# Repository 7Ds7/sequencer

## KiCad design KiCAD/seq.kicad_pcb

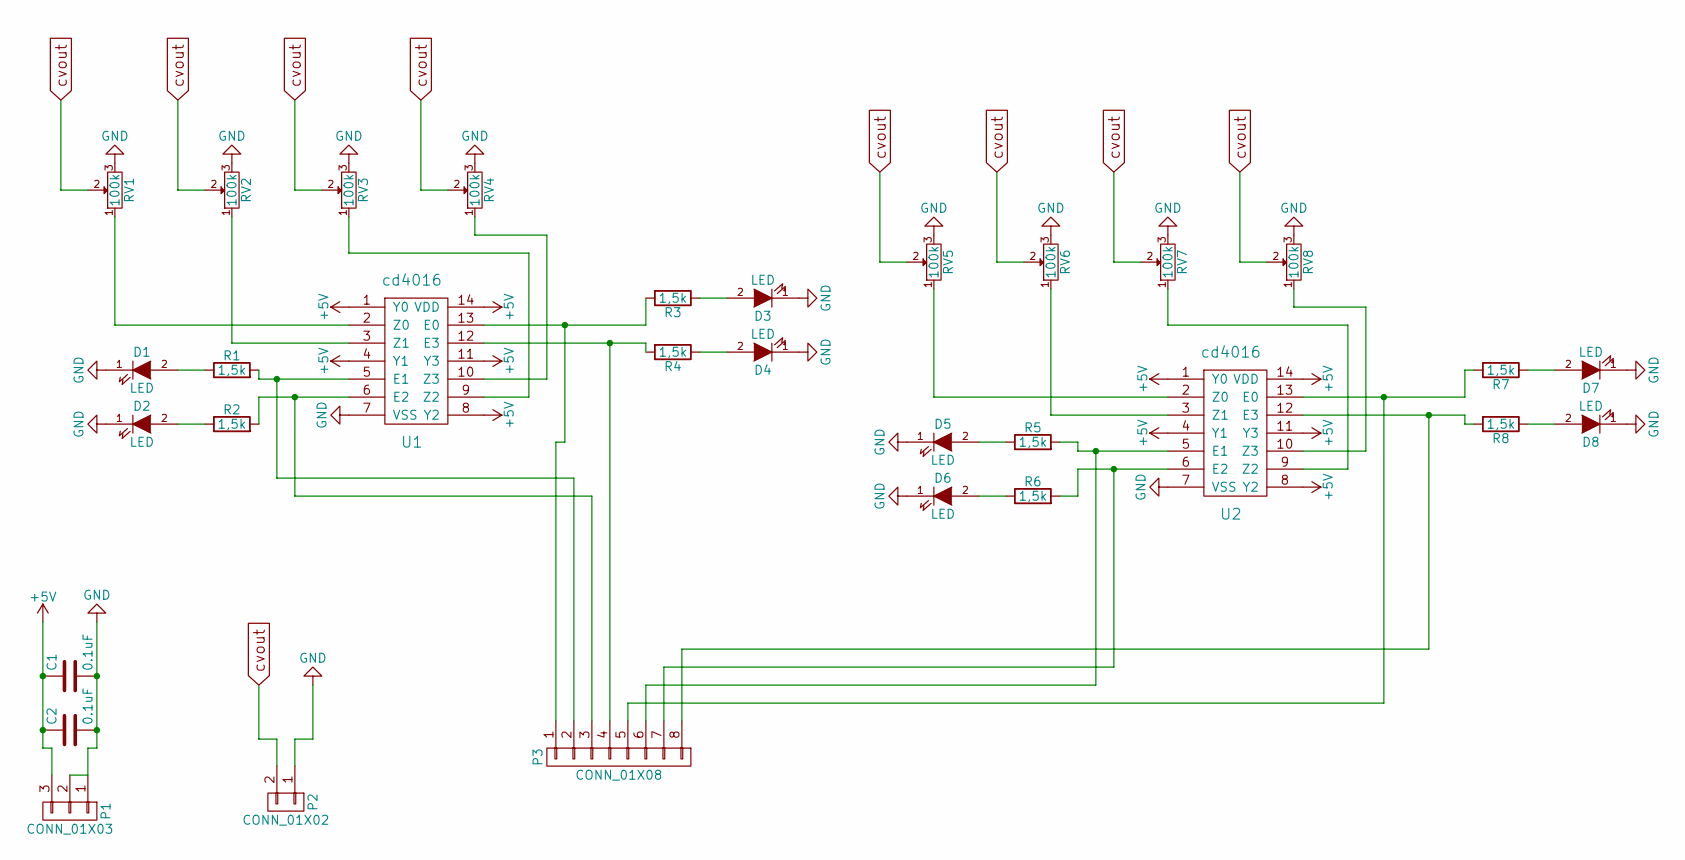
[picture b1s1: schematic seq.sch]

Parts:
C1, C2: 0.1uF; C_Disc_D6_P5
D1, D2, D3, D4, D5, D6, D7, D8: LED; LED-5MM
P1: CONN_01X03; Pin_Header_Straight_1x03
P2: CONN_01X02; Pin_Header_Straight_1x02
P3: CONN_01X08; Pin_Header_Straight_1x08
R1, R2, R3, R4, R5, R6, R7, R8: 1,5k; Resistor_Horizontal_RM15mm
RV1, RV2, RV3, RV4, RV5, RV6, RV7, RV8: 100k; Potentiometer_WirePads_largePads
U1, U2: cd4016; DIP-14_W7.62mm_LongPads

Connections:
+5V: C1.1, C2.1, P1.3, U1.1 (Y0), U1.4 (Y1), U1.8 (Y2), U1.11 (Y3), U1.14 (VDD), U2.1 (Y0), U2.4 (Y1), U2.8 (Y2), U2.11 (Y3), U2.14 (VDD)
GND: C1.2, C2.2, D1.1 (K), D2.1 (K), D3.1 (K), D4.1 (K), D5.1 (K), D6.1 (K), D7.1 (K), D8.1 (K), P1.1, P1.2, P2.1, RV1.3, RV2.3, RV3.3, RV4.3, RV5.3, RV6.3, RV7.3, RV8.3, U1.7 (VSS), U2.7 (VSS)
unnamed: D1.2 (A), R1.1
unnamed: D2.2 (A), R2.1
unnamed: D3.2 (A), R3.1
unnamed: D4.2 (A), R4.1
unnamed: D5.2 (A), R5.1
unnamed: D6.2 (A), R6.1
unnamed: D7.2 (A), R7.1
unnamed: D8.2 (A), R8.1
unnamed: P3.1, R3.2, U1.13 (E0)
unnamed: P3.2, R1.2, U1.5 (E1)
unnamed: P3.3, R2.2, U1.6 (E2)
unnamed: P3.4, R4.2, U1.12 (E3)
unnamed: P3.5, R7.2, U2.13 (E0)
unnamed: P3.6, R5.2, U2.5 (E1)
unnamed: P3.7, R6.2, U2.6 (E2)
unnamed: P3.8, R8.2, U2.12 (E3)
unnamed: RV1.1, U1.2 (Z0)
unnamed: RV2.1, U1.3 (Z1)
unnamed: RV3.1, U1.9 (Z2)
unnamed: RV4.1, U1.10 (Z3)
unnamed: RV5.1, U2.2 (Z0)
unnamed: RV6.1, U2.3 (Z1)
unnamed: RV7.1, U2.9 (Z2)
unnamed: RV8.1, U2.10 (Z3)
cvout: P2.2, RV1.2, RV2.2, RV3.2, RV4.2, RV5.2, RV6.2, RV7.2, RV8.2

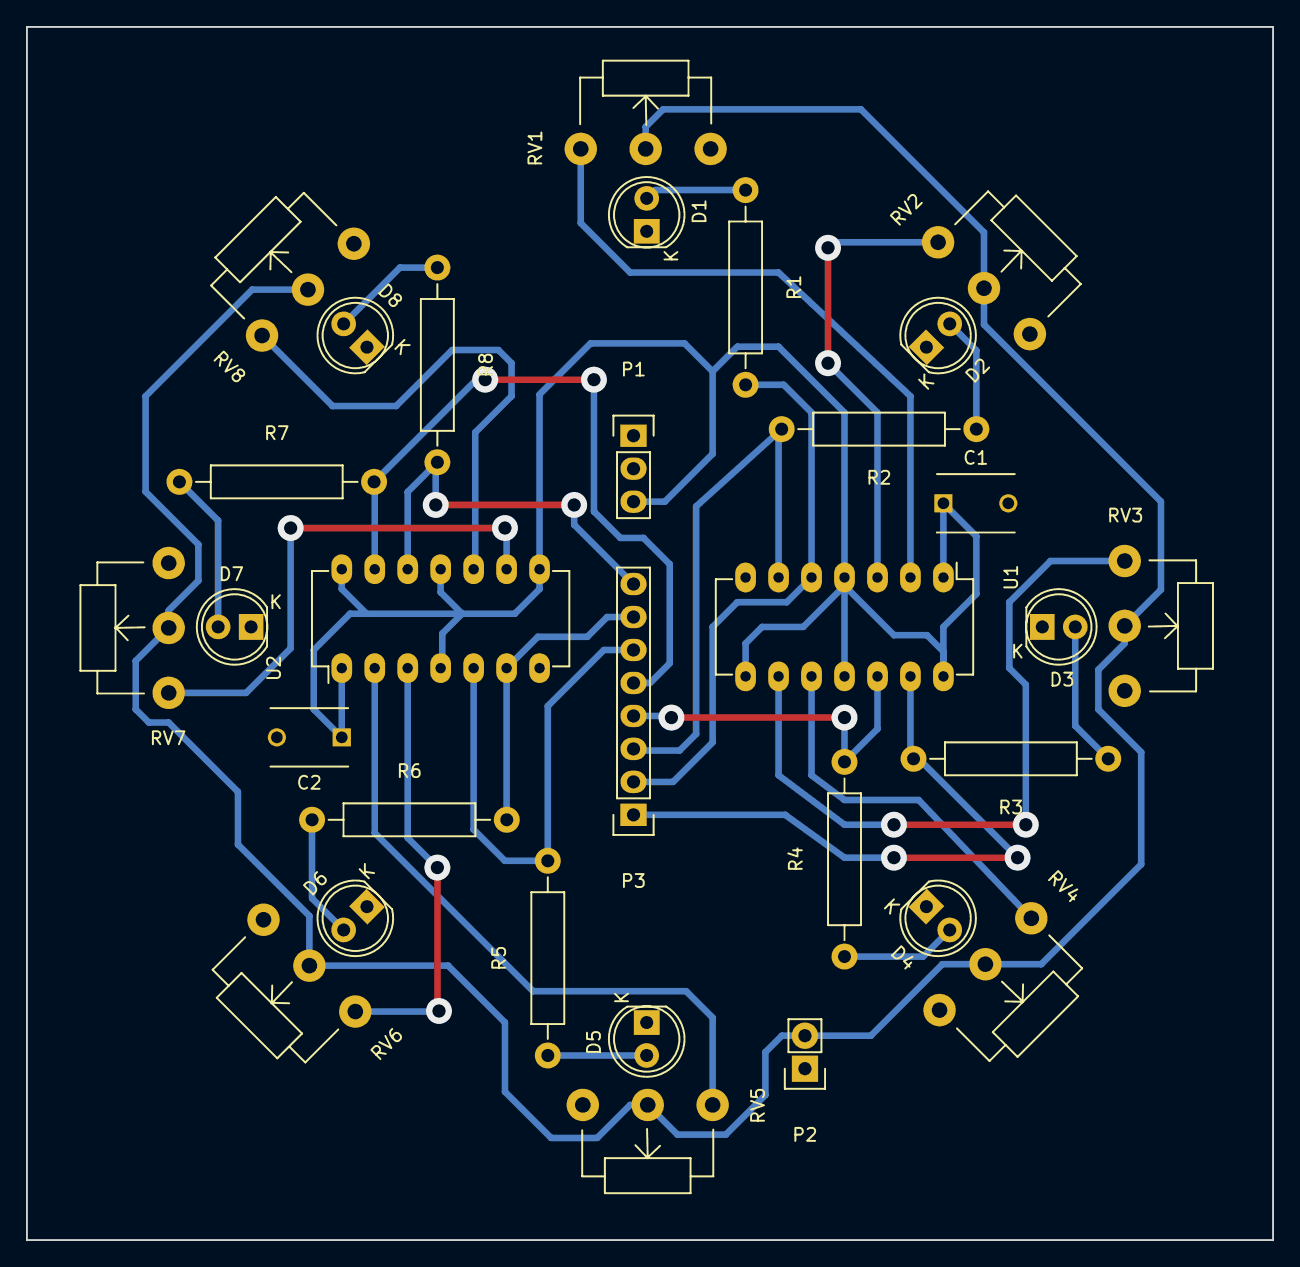
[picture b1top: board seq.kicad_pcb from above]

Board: 2 copper layers, 96.0 x 93.5 mm, 31 parts (0 on the bottom side), 27 nets.

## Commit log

2016-12-11 Added arduino sequencer
2016-12-11 added files sch and pcb
2016-12-11 library Kicad
2017-01-11 esquema errado
2017-01-11 limpeza de ficheiros
2017-01-11 added gate pin
2017-01-12 arduino sequencer simple
2017-01-26 debugging sequencer with all led pins low
2017-01-26 changed beat potentiometer to A0
2017-01-30 updated schematic
    added arduino mini and simple 5V power supply to the schematic. my
    library also updated with arduino mini schematic.
2019-02-20 Introduced multiplexer to only use 3 digital pins
2019-02-20 Added .DsStore to gitgignore
